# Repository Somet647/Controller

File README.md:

# Custom ATmega32U4 USB HID Gamepad

A custom USB gamepad designed and built around an ATmega32U4 microcontroller. This project started as a breadboard prototype using an Arduino and was developed into a standalone custom PCB, combining embedded firmware, digital and analog inputs, USB HID communication, and PCB design.

---

## Features

### Hardware & PCB Design
* **Custom ATmega32U4 Design:** Designed a standalone gamepad around the ATmega32U4, integrating the microcontroller, clock circuitry, USB interface, programming header, analog inputs, and digital inputs onto a custom PCB.
* **USB-C Interface:** Implemented a USB-C device interface with 5.1kΩ CC pull-down resistors, 22Ω D+/D− series resistors, and dedicated power decoupling for reliable communication.
* **Analog Input System:** Integrated analog data processing using the ATmega32U4's ADC channels to provide joystick functionality.
* **Power & Decoupling:** Distributed the +5V USB supply across the board with local 100nF and bulk 10μF capacitors to reduce noise and add stability.
* **External Clock:** Implemented a 16MHz crystal oscillator with 22pF load capacitors to provide the ATmega32U4 with a stable system clock.
* **ISP Programming:** Added a dedicated 6-pin AVR ISP header for directly programming the ATmega32U4 on the custom PCB.
* **PCB Layout:** Designed the complete schematic and multi-layer PCB layout in KiCad.

### Firmware
* **Standalone USB HID:** Configured the ATmega32U4 as a USB HID gamepad, providing direct PC compatibility without a secondary USB-to-UART bridge or custom PC software.
* **Analog Input Handling:** Used the ATmega32U4's 10-bit ADC to support 2 analog joysticks across 4 axes (X, Y, Rx, Ry).
* **Digital Input Handling:** Configured 14 button inputs using the MCU's internal pull-up resistors and active-low logic, eliminating the need for external pull-up components.
* **Low-Latency Input**: Sampled button and analog inputs at approximately 100 Hz using a 10 ms control loop for responsive controller input.
* **Input Mapping:** Developed a software mapping between the ATmega32U4 GPIO/ADC pins and the corresponding gamepad buttons and analog axes.

---

## Hardware Specifications

| Component            | Specification                      |
| -------------------- | ---------------------------------- |
| **MCU**              | ATmega32U4                         |
| **Supply**           | 5 V from USB                       |
| **USB Connector**    | USB-C                              |
| **USB Data**         | D+ / D− with 22 Ω series resistors |
| **CC Configuration** | 5.1 kΩ pull-downs on CC1/CC2       |
| **Digital Inputs**   | 14 buttons, internal pull-ups      |
| **Analog Inputs**    | 4 × 10-bit ADC channels            |
| **Analog Controls**  | 2 × dual-axis joysticks            |
| **System Clock**     | 16 MHz external crystal            |
| **ISP**              | 6-pin AVR ISP header               |
| **PCB**              | Custom multi-layer PCB             |
| **Design Software**  | KiCad                              |

---

## Repository Structure

```text
├── firmware/         # C++ / Arduino controller logic and USB HID descriptors
├── hardware/         # KiCad schematics, PCB board layout, and Gerber manufacturing files
└── README.md         # Project technical summary

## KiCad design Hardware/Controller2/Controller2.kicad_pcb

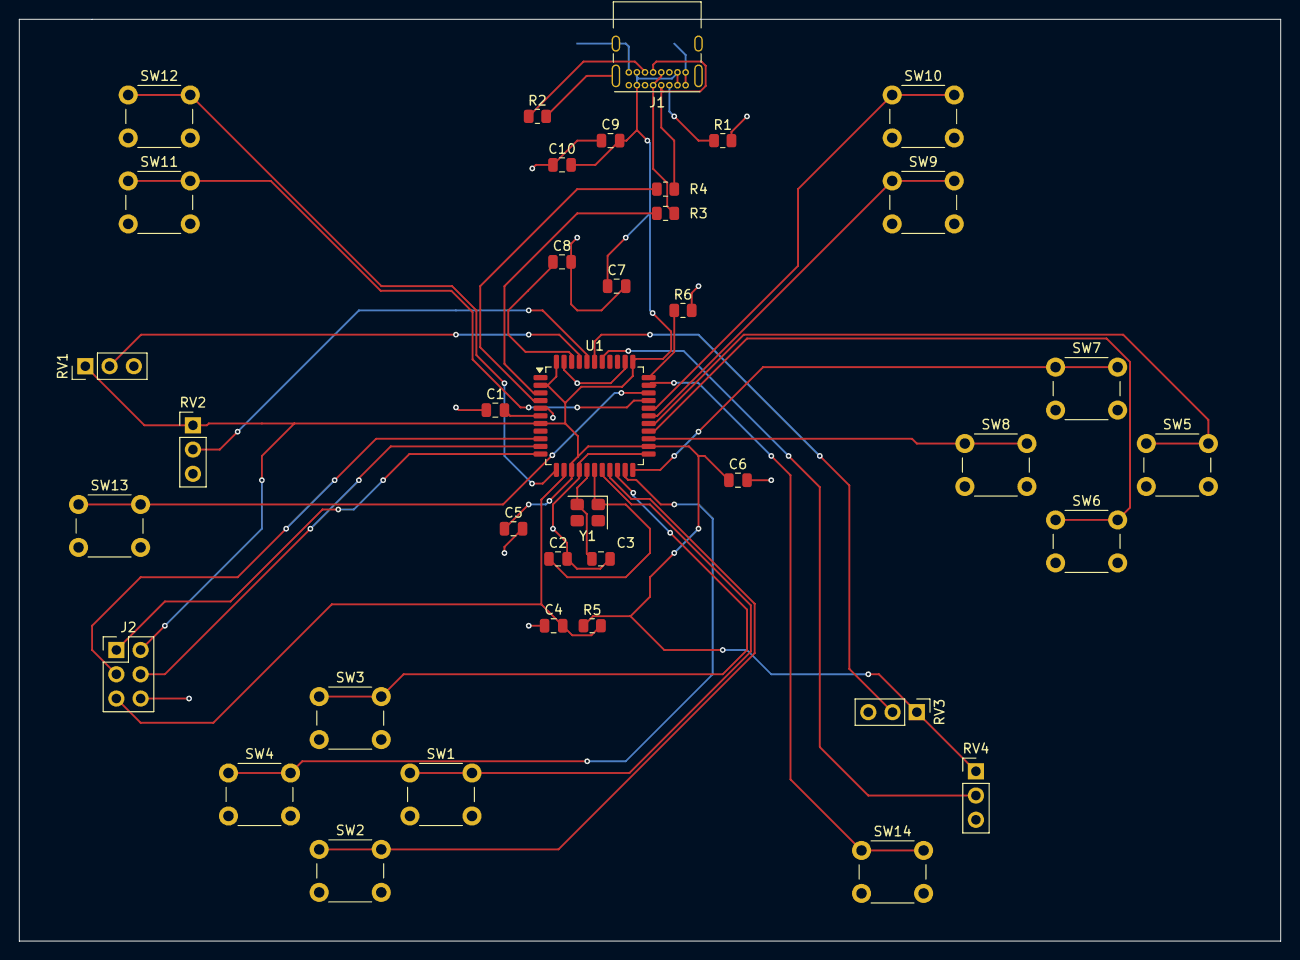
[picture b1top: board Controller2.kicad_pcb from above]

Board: 2 copper layers, 132.1 x 96.5 mm, 38 parts (0 on the bottom side), 35 nets.

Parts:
C1: 1u; C_0805_2012Metric
C2, C3: 22p; C_0805_2012Metric
C4, C5, C6, C8: 100n; C_0805_2012Metric
C7, C9: 10u; C_0805_2012Metric
C10: 0.1u; C_0805_2012Metric
J1: USB_C_Receptacle_USB2.0_16P; USB_C_Receptacle_GCT_USB4085
J2: Conn_02x03_Odd_Even; PinHeader_2x03_P2.54mm_Vertical
R1, R2: 5.1k; R_0805_2012Metric
R3, R4: 22; R_0805_2012Metric
R5, R6: 10k; R_0805_2012Metric
RV1, RV2, RV3, RV4: R_Potentiometer; PinHeader_1x03_P2.54mm_Vertical
SW1, SW2, SW3, SW4, SW5, SW6, SW7, SW8, SW9, SW10, SW11, SW12, SW13, SW14: SW_Push; SW_PUSH_6mm
U1: ATmega32U4-A; TQFP-44_10x10mm_P0.8mm
Y1: 16MHz; Crystal_SMD_3225-4Pin_3.2x2.5mm

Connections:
+5V: C5.1, C6.1, C7.1, C9.2, C10.2, J1.A4 (VBUS), J1.A9 (VBUS), J1.B4 (VBUS), J1.B9 (VBUS), J2.2, R5.1, RV1.1, RV2.1, RV3.1, RV4.1, U1.2 (UVCC), U1.7 (VBUS), U1.14 (VCC), U1.24 (AVCC), U1.34 (VCC), U1.44 (AVCC)
GND: C1.1, C2.2, C3.2, C4.1, C5.2, C6.2, C7.2, C8.2, C9.1, C10.1, J1.A1 (GND), J1.A12 (GND), J1.B1 (GND), J1.B12 (GND), J1.SH (SHIELD), J2.6, R1.2, R2.2, R6.2, RV1.3, RV2.3, RV3.3, RV4.3, SW1.2, SW2.2, SW3.2, SW4.2, SW5.2, SW6.2, SW7.2, SW8.2, SW9.2, SW10.2, SW11.2, SW12.2, SW13.2, SW14.2, U1.5 (UGND), U1.15 (GND), U1.23 (GND), U1.35 (GND), U1.43 (GND)
unnamed: J1.A5 (CC1), R1.1
unnamed: J1.B5 (CC2), R2.1
unnamed: J1.A6 (D+), J1.B6 (D+), R4.1
unnamed: J1.A7 (D-), J1.B7 (D-), R3.1
unnamed: J2.1, U1.11 (PB3)
unnamed: J2.3, U1.9 (PB1)
unnamed: J2.4, U1.10 (PB2)
unnamed: C4.2, J2.5, R5.2, U1.13 (~RESET)
unnamed: C8.1, U1.42 (AREF)
unnamed: R4.2, U1.4 (D+)
unnamed: R3.2, U1.3 (D-)
unnamed: SW9.1, U1.28 (PB4)
unnamed: SW10.1, U1.29 (PB5)
unnamed: SW11.1, U1.30 (PB6)
unnamed: SW12.1, U1.12 (PB7)
unnamed: SW13.1, U1.31 (PC6)
unnamed: SW14.1, U1.32 (PC7)
unnamed: SW1.1, U1.18 (PD0)
unnamed: SW2.1, U1.19 (PD1)
unnamed: SW3.1, U1.20 (PD2)
unnamed: SW4.1, U1.21 (PD3)
unnamed: SW8.1, U1.25 (PD4)
unnamed: SW7.1, U1.22 (PD5)
unnamed: SW6.1, U1.26 (PD6)
unnamed: SW5.1, U1.27 (PD7)
unnamed: RV1.2, U1.41 (PF0)
unnamed: RV2.2, U1.40 (PF1)
unnamed: RV3.2, U1.39 (PF4)
unnamed: RV4.2, U1.38 (PF5)
unnamed: C1.2, U1.6 (UCAP)
unnamed: C2.1, U1.17 (XTAL1), Y1.1
unnamed: C3.1, U1.16 (XTAL2), Y1.2
unnamed: R6.1, U1.33 (~HWB/PE2)
